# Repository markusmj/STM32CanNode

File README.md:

# STM32CanNode

Software still highly unstable and updating code all the time. Use at your own risk!!!

Projects goal is to make a simple Can Node which will read 10 analog inputs and send their data to Canbus. Idea is also to design simple connecting PCB where common and cheap STM32F103C8T6 Blue Pill Development Board and MCP2515+TJA1050 Can module can be used to create compact package with Analog/digital ports and Can capabilities.

Some key features of selected hardware:
- Fast SPI bus 18MHz
- 1000kbit/s Can bus
- Fast 12-bit ADC
- 10 analog channels

STM32Duino:
http://www.stm32duino.com/

Used MCP2515 library:
https://github.com/Seeed-Studio/CAN_BUS_Shield

More info on STM32 Development Board Nicknamed Blue Pill:
http://wiki.stm32duino.com/index.php?title=Blue_Pill

MCP 2515 Module used:
https://www.banggood.com/D33-MCP2515-CAN-Bus-Module-TJA1050-Receiver-SPI-Protocol-p-1015302.html

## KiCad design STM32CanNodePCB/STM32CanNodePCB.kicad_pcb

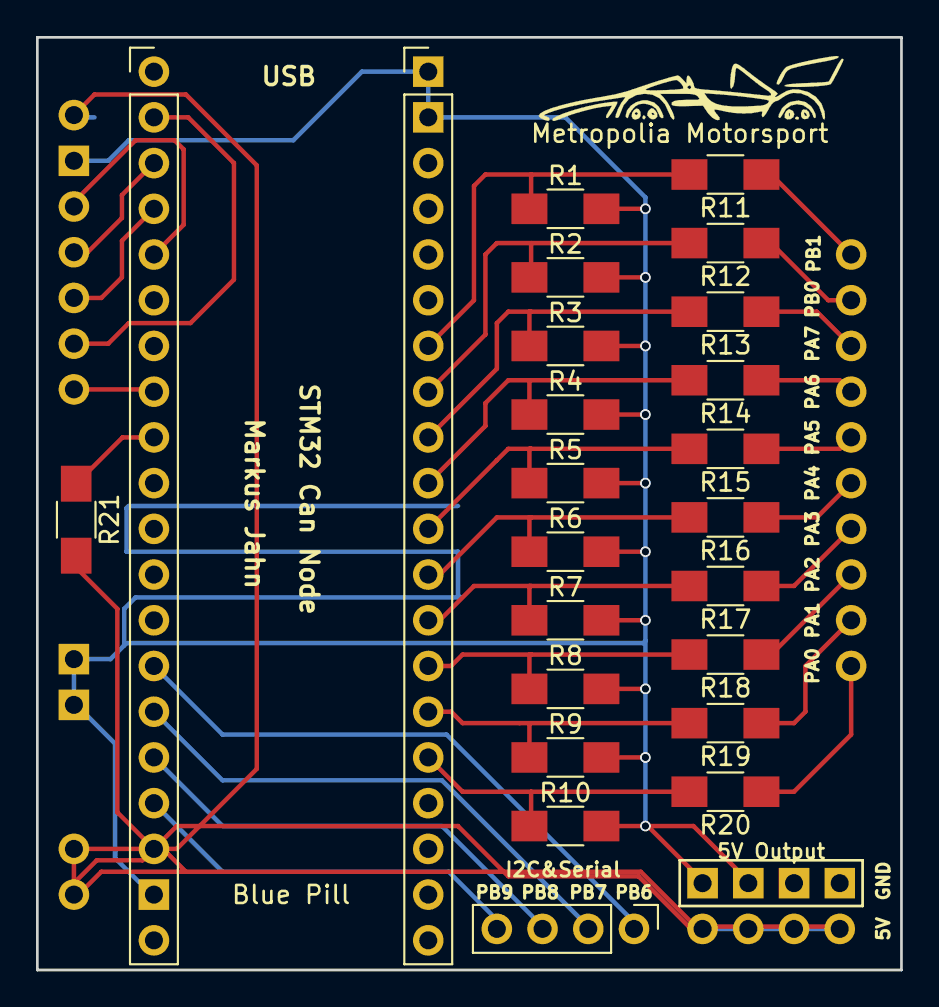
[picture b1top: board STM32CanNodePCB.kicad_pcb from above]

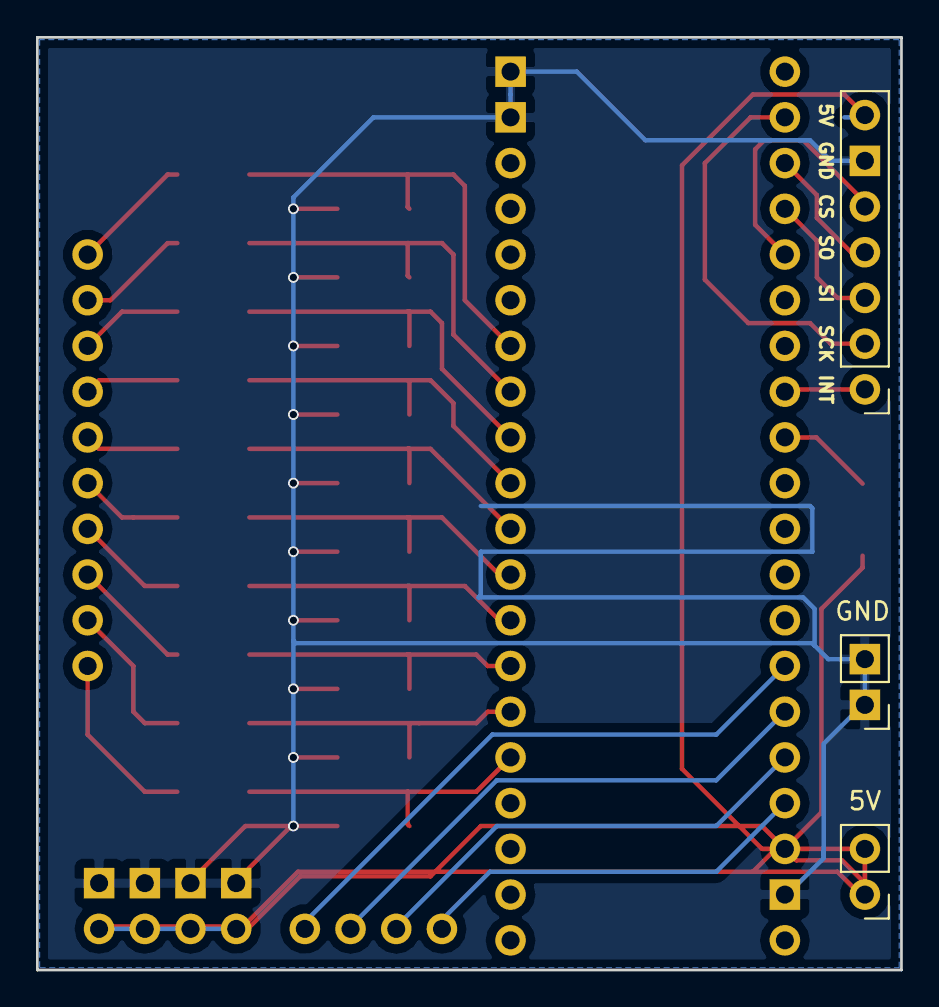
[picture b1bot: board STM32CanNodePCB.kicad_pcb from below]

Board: 2 copper layers, 48.0 x 51.8 mm, 28 parts (3 on the bottom side), 32 nets.

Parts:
5V1: 5V; Pin_Header_Straight_1x02_Pitch2.54mm
GND1: GND; Pin_Header_Straight_1x02_Pitch2.54mm
J1: Blue Pill; BluePill
J2: Metropolia Motorsport; Analoginput
J3: MCP2515Connector
J4: I2C&Serial; Pin_Header_Straight_1x04_Pitch2.54mm
J6: 5V Output; 5VOutput
R1, R2, R3, R4, R5, R6, R7, R8, R9, R10: 1k; R_1206_HandSoldering
R11, R12, R13, R14, R15, R16, R17, R18, R19, R20: 4.7k; R_1206_HandSoldering
R21: 1.8k; R_1206_HandSoldering

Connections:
GND: GND1.1, GND1.2, J1.GND, J3.GND, J6.1b, J6.2b, J6.3b, J6.4b, R1.2, R2.2, R3.2, R4.2, R5.2, R6.2, R7.2, R8.2, R9.2, R10.2
unnamed: 5V1.1, 5V1.2, J1.5V, J3.VCC, J6.1a, J6.2a, J6.3a, J6.4a, R21.2
unnamed: J1.PA0, R10.1, R20.2
unnamed: J1.PA1, R9.1, R19.2
unnamed: J1.PA2, R8.1, R18.2
unnamed: J1.PA3, R7.1, R17.2
unnamed: J1.PA4, R6.1, R16.2
unnamed: J1.PA5, R5.1, R15.2
unnamed: J1.PA6, R4.1, R14.2
unnamed: J1.PA7, R3.1, R13.2
unnamed: J1.PA8, J3.CS
unnamed: J1.PA11, J3.INT
unnamed: J1.PA12, R21.1
unnamed: J1.PB0, R2.1, R12.2
unnamed: J1.PB1, R1.1, R11.2
unnamed: J1.PB13, J3.SCK
unnamed: J1.PB14, J3.MISO
unnamed: J1.PB15, J3.MOSI
unnamed: J2.PA0, R20.1
unnamed: J2.PA1, R19.1
unnamed: J2.PA2, R18.1
unnamed: J2.PA3, R17.1
unnamed: J2.PA4, R16.1
unnamed: J2.PA5, R15.1
unnamed: J2.PA6, R14.1
unnamed: J2.PA7, R13.1
unnamed: J2.PB0, R12.1
unnamed: J2.PB1, R11.1
PB6: J1.PB6, J4.1
PB7: J1.PB7, J4.2
PB8: J1.PB8, J4.3
PB9: J1.PB9, J4.4

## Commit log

2017-12-22 First version of project description
2017-12-22 New license
2017-12-22 Create LICENSE
2017-12-22 More links to HW/SW
2017-12-22 Adding Comments
2017-12-22 Updt
2017-12-23 Faster ADC Read
2017-12-23 Added Warning
2017-12-23 Added pin definitions
2017-12-25 Added averaging
    Averaging increases accuracy of analog reads but slows down looptime/frequency.
2017-12-26 Added frequency reader code
2019-01-23 Added Kicad PCB files
2019-01-23 MCP2515 Schema Added.
